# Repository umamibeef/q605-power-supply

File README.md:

# q605-power-supply
A replacement power supply for the Macintosh Quadra 605 featuring a soft power switch.

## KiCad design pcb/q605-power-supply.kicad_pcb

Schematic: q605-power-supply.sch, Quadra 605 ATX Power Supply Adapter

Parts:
C1, C2: 0.1u; C_Disc_D3.0mm_W1.6mm_P2.50mm
C3: 330n; CP_Radial_D4.0mm_P2.00mm
C4: 1u; CP_Radial_D4.0mm_P2.00mm
J1: ATX-24; Molex_Mini-Fit_Jr_5566-24A_2x12_P4.20mm_Vertical
J2, J3: Screw_Terminal_01x02; TerminalBlock_RND_205-00001_1x02_P5.00mm_Horizontal
J4: Screw_Terminal_01x05; TerminalBlock_RND_205-00004_1x05_P5.00mm_Horizontal
J5: Conn_01x06; PinHeader_1x06_P2.54mm_Vertical
Q1: Q_NPN_EBC; TO-92
R1: 1k; R_Axial_DIN0204_L3.6mm_D1.6mm_P5.08mm_Horizontal
R2, R4, R5, R6, R7: 10k; R_Axial_DIN0204_L3.6mm_D1.6mm_P5.08mm_Horizontal
R3: 0; R_Axial_DIN0204_L3.6mm_D1.6mm_P5.08mm_Horizontal
U1: PIC16F18313; DIP-8_W7.62mm
U2: MC79M05_TO220; TO-220-3_Vertical

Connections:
+5V: J1.4 (+5V), J1.6 (+5V), J1.21 (+5V), J1.22 (+5V), J1.23 (+5V), J4.3
+5VA: C2.1, J1.9 (+5VSB), J5.2, R2.2, R3.2, R5.2, R6.2, U1.1 (VDD)
+12V: J1.10 (+12V), J1.11 (+12V), J4.2
-5V: C4.2, J4.1, U2.3 (VO)
-12V: C3.2, J1.14 (-12V), U2.2 (VI)
/ATX_PWR_OK: J1.8 (PWR_OK), R7.2
/ICSP_CLK: J5.5, U1.6 (RA1/ICSPCLK)
/ICSP_DAT: J5.4, R7.1, U1.7 (RA0/ICSPDAT)
/LED_A: J3.2, R3.1
/LED_K: J3.1, Q1.3
/PWR_LED: R4.1, U1.3 (RA4)
/PWR_SW: C1.1, R1.1, R2.1, U1.5 (RA2)
/~ATX_PWR_ON~: J1.16 (PS_ON#), R5.1, U1.2 (RA5)
/~MCLR~: J5.1, R6.1, U1.4 (VPP/~MCLR~/RA3)
GND: C1.2, C2.2, C3.1, C4.1, J1.3 (GND), J1.5 (GND), J1.7 (GND), J1.15 (GND), J1.17 (GND), J1.18 (GND), J1.19 (GND), J1.24 (GND), J2.1, J4.4, J4.5, J5.3, Q1.1, U1.8 (VSS), U2.1 (GND)
unnamed: J1.1 (+3.3V), J1.2 (+3.3V), J1.12 (+3.3V), J1.13 (+3.3V)
unnamed: J2.2, R1.2
unnamed: Q1.2, R4.2

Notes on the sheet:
Microcontroller + Programming
24-pin ATX Connector
Q605 PSU Output + Power Switch + Power LED
-12V to -5V LDO

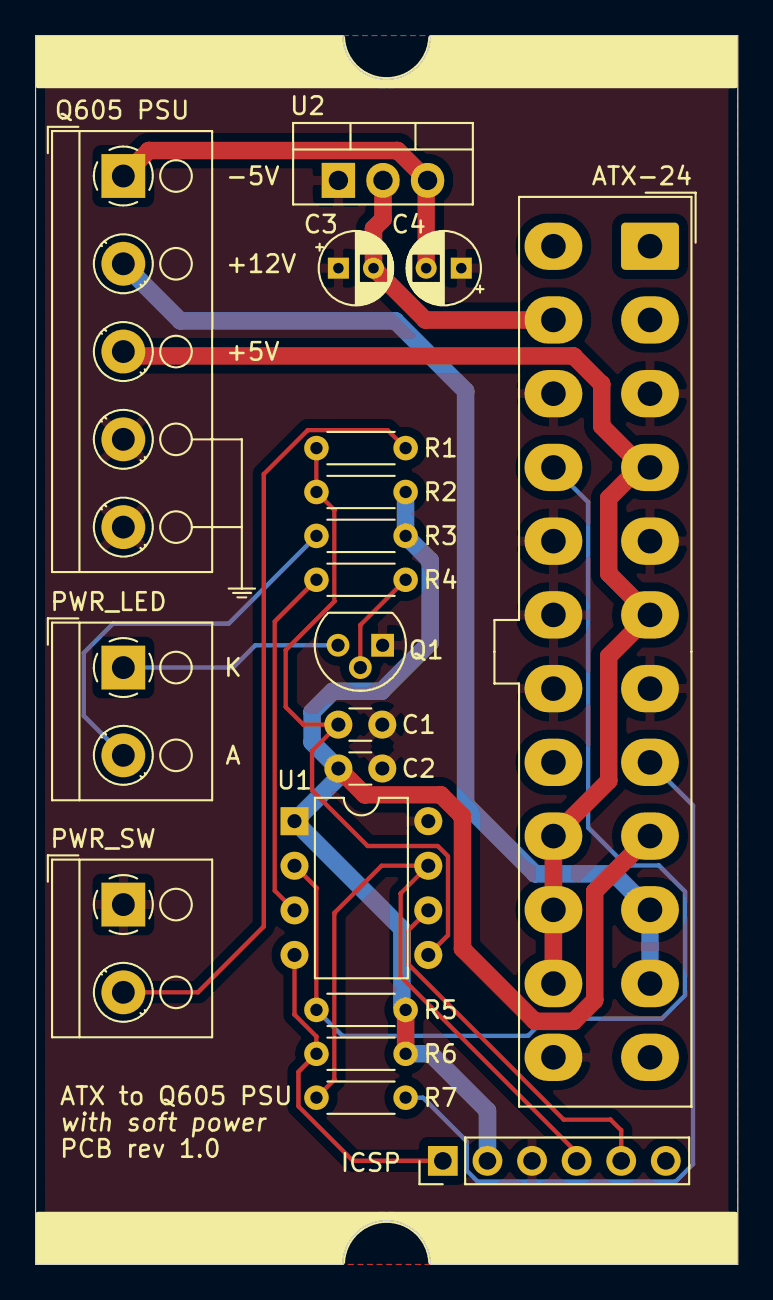
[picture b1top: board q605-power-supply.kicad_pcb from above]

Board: 2 copper layers, 40.0 x 70.0 mm, 19 parts (0 on the bottom side), 18 nets.

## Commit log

2020-10-19 First draft, still missing inverting 5V supply
2020-10-22 Finished schematic placement and annotation
2020-10-23 Added programming header and assigned footprints
2020-10-24 Finished routing
2020-10-29 Moving to PCB folder
2020-11-12 Starting FW project
